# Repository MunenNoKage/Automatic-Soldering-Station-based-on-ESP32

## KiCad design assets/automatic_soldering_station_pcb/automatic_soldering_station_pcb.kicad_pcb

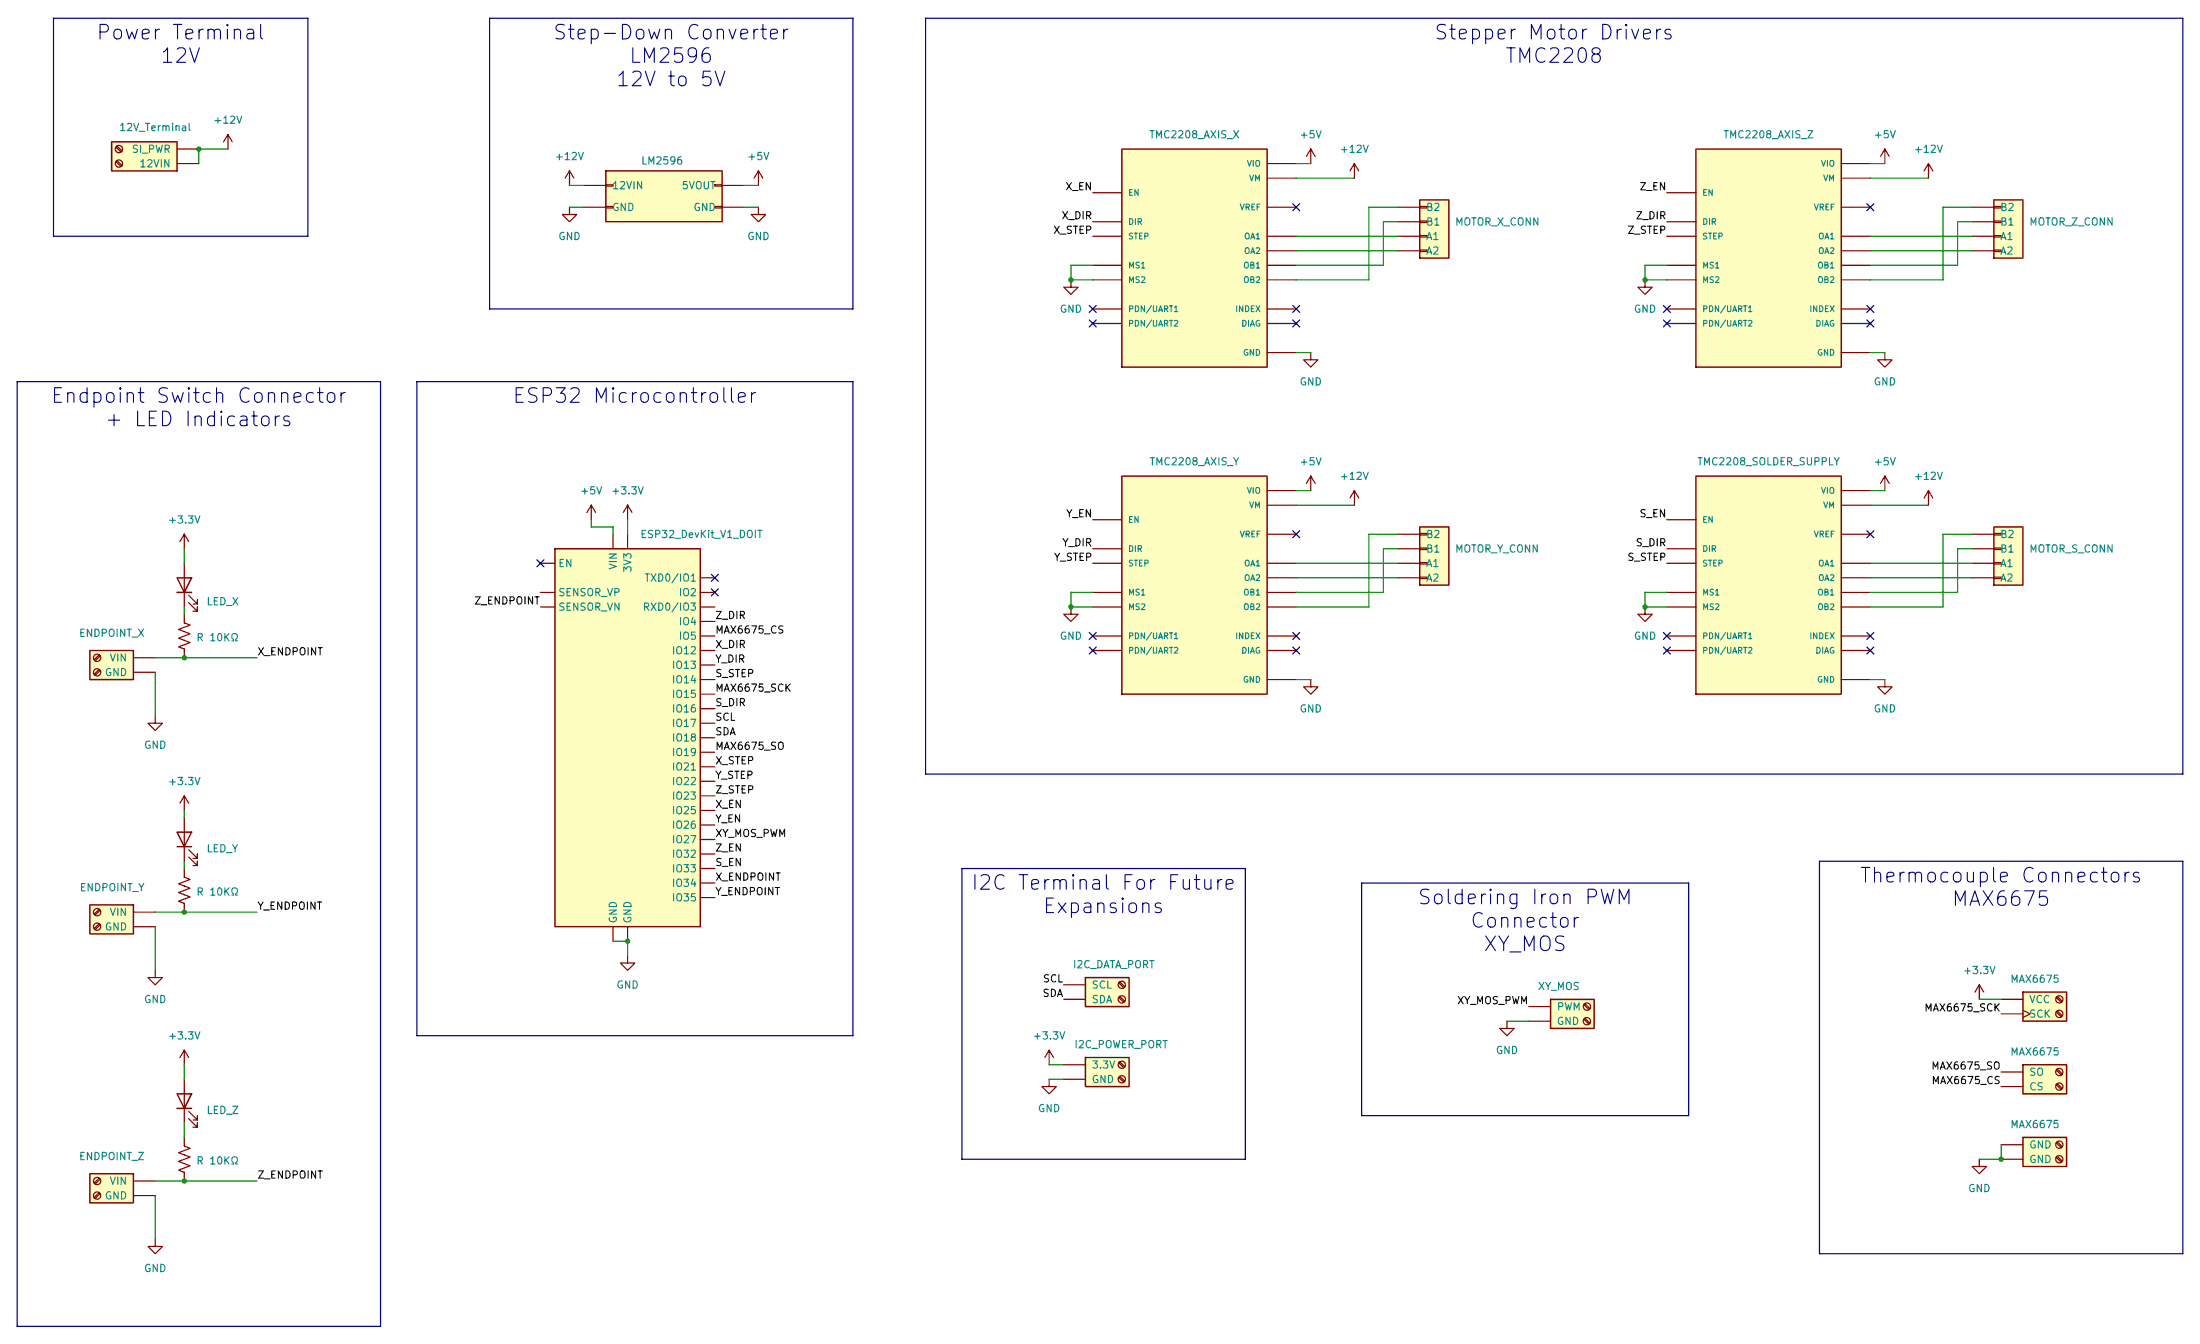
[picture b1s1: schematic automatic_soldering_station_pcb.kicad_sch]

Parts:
12V2: 12V_Terminal; TerminalBlock_MetzConnect_Type055_RT01502HDWU_1x02_P5.00mm_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
D1: LED_X; LED_D5.0mm
D2: LED_Y; LED_D5.0mm
D3: LED_Z; LED_D5.0mm
ENDPOINT_X1: ENDPOINT_X; TerminalBlock_MetzConnect_Type055_RT01502HDWU_1x02_P5.00mm_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
ENDPOINT_Y1: ENDPOINT_Y; TerminalBlock_MetzConnect_Type055_RT01502HDWU_1x02_P5.00mm_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
ENDPOINT_Y2: I2C_POWER_PORT; TerminalBlock_MetzConnect_Type055_RT01502HDWU_1x02_P5.00mm_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
ENDPOINT_Z1: ENDPOINT_Z; TerminalBlock_MetzConnect_Type055_RT01502HDWU_1x02_P5.00mm_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
ESP32_DevKit_V1_DOIT1: ESP32_DevKit_V1_DOIT; esp32_devkit_v1_doit
J1: XY_MOS; TerminalBlock_MetzConnect_Type055_RT01502HDWU_1x02_P5.00mm_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
J2, J3, J4: MAX6675; TerminalBlock_MetzConnect_Type055_RT01502HDWU_1x02_P5.00mm_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
J5: I2C_DATA_PORT; TerminalBlock_MetzConnect_Type055_RT01502HDWU_1x02_P5.00mm_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
LM2596: LM2596; LM2596_Board
MOTOR_S_CONN1: MOTOR_S_CONN; JST_PH_B4B-PH-K_1x04_P2.00mm_Vertical
MOTOR_X_CONN1: MOTOR_X_CONN; JST_PH_B4B-PH-K_1x04_P2.00mm_Vertical
MOTOR_Y_CONN1: MOTOR_Y_CONN; JST_PH_B4B-PH-K_1x04_P2.00mm_Vertical
MOTOR_Z_CONN1: MOTOR_Z_CONN; JST_PH_B4B-PH-K_1x04_P2.00mm_Vertical
R1, R2, R3: R 10KΩ; R_Axial_DIN0207_L6.3mm_D2.5mm_P7.62mm_Horizontal
TMC2208_AXIS_S1: TMC2208_SOLDER_SUPPLY; MODULE_TMC2208_SILENTSTEPSTICK
TMC2208_AXIS_X1: TMC2208_AXIS_X; MODULE_TMC2208_SILENTSTEPSTICK
TMC2208_AXIS_Y1: TMC2208_AXIS_Y; MODULE_TMC2208_SILENTSTEPSTICK
TMC2208_AXIS_Z1: TMC2208_AXIS_Z; MODULE_TMC2208_SILENTSTEPSTICK

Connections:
+3.3V: D1.2 (A), D2.2 (A), D3.2 (A), ENDPOINT_Y2.1 (3.3V), ESP32_DevKit_V1_DOIT1.16 (3V3), J3.1 (VCC)
+5V: ESP32_DevKit_V1_DOIT1.15 (VIN), LM2596.2 (5VOUT), TMC2208_AXIS_S1.JP2_7 (VIO), TMC2208_AXIS_X1.JP2_7 (VIO), TMC2208_AXIS_Y1.JP2_7 (VIO), TMC2208_AXIS_Z1.JP2_7 (VIO)
+12V: 12V2.1 (12VIN), 12V2.2 (SI_PWR), LM2596.0 (12VIN), TMC2208_AXIS_S1.JP2_1 (VM), TMC2208_AXIS_X1.JP2_1 (VM), TMC2208_AXIS_Y1.JP2_1 (VM), TMC2208_AXIS_Z1.JP2_1 (VM)
/MAX6675_CS: ESP32_DevKit_V1_DOIT1.23 (IO5), J4.2 (CS)
/MAX6675_SCK: ESP32_DevKit_V1_DOIT1.18 (IO15), J3.2 (SCK)
/MAX6675_SO: ESP32_DevKit_V1_DOIT1.25 (IO19), J4.1 (SO)
/SCL: ESP32_DevKit_V1_DOIT1.22 (IO17), J5.1 (SCL)
/SDA: ESP32_DevKit_V1_DOIT1.24 (IO18), J5.2 (SDA)
/S_DIR: ESP32_DevKit_V1_DOIT1.21 (IO16), TMC2208_AXIS_S1.JP1_1 (DIR)
/S_EN: ESP32_DevKit_V1_DOIT1.7 (IO33), TMC2208_AXIS_S1.JP1_8 (EN)
/S_STEP: ESP32_DevKit_V1_DOIT1.11 (IO14), TMC2208_AXIS_S1.JP1_2 (STEP)
/XY_MOS_PWM: ESP32_DevKit_V1_DOIT1.10 (IO27), J1.1 (PWM)
/X_DIR: ESP32_DevKit_V1_DOIT1.12 (IO12), TMC2208_AXIS_X1.JP1_1 (DIR)
/X_EN: ESP32_DevKit_V1_DOIT1.8 (IO25), TMC2208_AXIS_X1.JP1_8 (EN)
/X_ENDPOINT: ENDPOINT_X1.1 (VIN), ESP32_DevKit_V1_DOIT1.4 (IO34), R1.2
/X_STEP: ESP32_DevKit_V1_DOIT1.26 (IO21), TMC2208_AXIS_X1.JP1_2 (STEP)
/Y_DIR: ESP32_DevKit_V1_DOIT1.13 (IO13), TMC2208_AXIS_Y1.JP1_1 (DIR)
/Y_EN: ESP32_DevKit_V1_DOIT1.9 (IO26), TMC2208_AXIS_Y1.JP1_8 (EN)
/Y_ENDPOINT: ENDPOINT_Y1.1 (VIN), ESP32_DevKit_V1_DOIT1.5 (IO35), R2.2
/Y_STEP: ESP32_DevKit_V1_DOIT1.29 (IO22), TMC2208_AXIS_Y1.JP1_2 (STEP)
/Z_DIR: ESP32_DevKit_V1_DOIT1.20 (IO4), TMC2208_AXIS_Z1.JP1_1 (DIR)
/Z_EN: ESP32_DevKit_V1_DOIT1.6 (IO32), TMC2208_AXIS_Z1.JP1_8 (EN)
/Z_ENDPOINT: ENDPOINT_Z1.1 (VIN), ESP32_DevKit_V1_DOIT1.3 (SENSOR_VN), R3.2
/Z_STEP: ESP32_DevKit_V1_DOIT1.30 (IO23), TMC2208_AXIS_Z1.JP1_2 (STEP)
GND: ENDPOINT_X1.2 (GND), ENDPOINT_Y1.2 (GND), ENDPOINT_Y2.2 (GND), ENDPOINT_Z1.2 (GND), ESP32_DevKit_V1_DOIT1.14 (GND), ESP32_DevKit_V1_DOIT1.17 (GND), J1.2 (GND), J2.1 (GND), J2.2 (GND), LM2596.1 (GND), LM2596.3 (GND), TMC2208_AXIS_S1.JP1_6 (MS2), TMC2208_AXIS_S1.JP1_7 (MS1), TMC2208_AXIS_S1.JP2_2 (GND), TMC2208_AXIS_S1.JP2_8 (GND), TMC2208_AXIS_X1.JP1_6 (MS2), TMC2208_AXIS_X1.JP1_7 (MS1), TMC2208_AXIS_X1.JP2_2 (GND), TMC2208_AXIS_X1.JP2_8 (GND), TMC2208_AXIS_Y1.JP1_6 (MS2), TMC2208_AXIS_Y1.JP1_7 (MS1), TMC2208_AXIS_Y1.JP2_2 (GND), TMC2208_AXIS_Y1.JP2_8 (GND), TMC2208_AXIS_Z1.JP1_6 (MS2), TMC2208_AXIS_Z1.JP1_7 (MS1), TMC2208_AXIS_Z1.JP2_2 (GND), TMC2208_AXIS_Z1.JP2_8 (GND)
unnamed: D1.1 (K), R1.1
unnamed: D2.1 (K), R2.1
unnamed: D3.1 (K), R3.1
unnamed: MOTOR_S_CONN1.2 (A1), TMC2208_AXIS_S1.JP2_4 (OA1)
unnamed: MOTOR_S_CONN1.1 (A2), TMC2208_AXIS_S1.JP2_3 (OA2)
unnamed: MOTOR_S_CONN1.3 (B1), TMC2208_AXIS_S1.JP2_5 (OB1)
unnamed: MOTOR_S_CONN1.4 (B2), TMC2208_AXIS_S1.JP2_6 (OB2)
unnamed: MOTOR_X_CONN1.2 (A1), TMC2208_AXIS_X1.JP2_4 (OA1)
unnamed: MOTOR_X_CONN1.1 (A2), TMC2208_AXIS_X1.JP2_3 (OA2)
unnamed: MOTOR_X_CONN1.3 (B1), TMC2208_AXIS_X1.JP2_5 (OB1)
unnamed: MOTOR_X_CONN1.4 (B2), TMC2208_AXIS_X1.JP2_6 (OB2)
unnamed: MOTOR_Y_CONN1.2 (A1), TMC2208_AXIS_Y1.JP2_4 (OA1)
unnamed: MOTOR_Y_CONN1.1 (A2), TMC2208_AXIS_Y1.JP2_3 (OA2)
unnamed: MOTOR_Y_CONN1.3 (B1), TMC2208_AXIS_Y1.JP2_5 (OB1)
unnamed: MOTOR_Y_CONN1.4 (B2), TMC2208_AXIS_Y1.JP2_6 (OB2)
unnamed: MOTOR_Z_CONN1.2 (A1), TMC2208_AXIS_Z1.JP2_4 (OA1)
unnamed: MOTOR_Z_CONN1.1 (A2), TMC2208_AXIS_Z1.JP2_3 (OA2)
unnamed: MOTOR_Z_CONN1.3 (B1), TMC2208_AXIS_Z1.JP2_5 (OB1)
unnamed: MOTOR_Z_CONN1.4 (B2), TMC2208_AXIS_Z1.JP2_6 (OB2)

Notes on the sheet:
Step-Down Converter LM2596 12V to 5V
ESP32 Microcontroller
Endpoint Switch Connector + LED Indicators
I2C Terminal For Future Expansions
Thermocouple Connectors MAX6675
Soldering Iron PWM Connector XY_MOS
Power Terminal 12V
Stepper Motor Drivers TMC2208

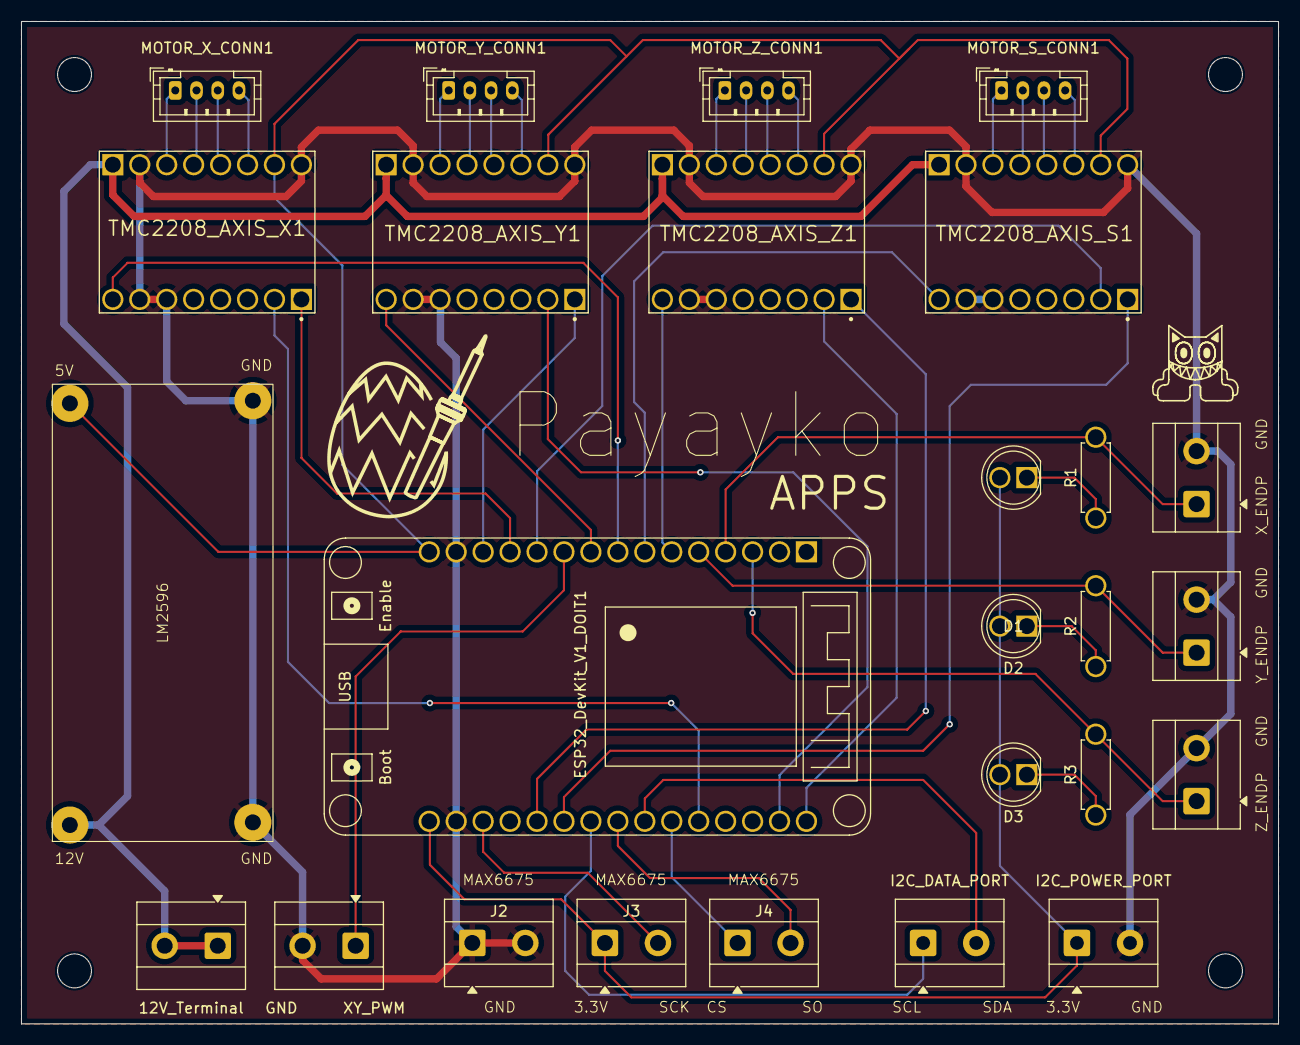
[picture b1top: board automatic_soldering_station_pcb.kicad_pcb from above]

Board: 2 copper layers, 118.5 x 94.5 mm, 30 parts (0 on the bottom side), 44 nets.

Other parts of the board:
H1, H2, H3, H4: MountingHole_3.2mm_M3

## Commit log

2025-11-20 chore: update 3d models for pcb holder
2025-11-20 chore: remove all deprecated directories
2025-11-20 chore: remove deprecated gcode_executor
2025-11-23 feat: update acceleration and deceleration logic and control
2025-11-23 feat: make calibration and movements faster, fix calibration glitch on endpoint
2025-11-23 pcb: add pcb project with complete project scheme
2025-11-30 pcb: add autorouted results
2025-12-01 pcb: add buck converter and reroute pcb manually
2025-12-08 pcb: polish routing
2025-12-08 pcb: fix printer specific mistakes
2025-12-09 Add manual control
2025-12-09 feat: update web interface
2025-12-09 pcb: reduce size of pcb
2025-12-09 feat: control z-position manually
2025-12-09 chore: add max measured motor positions to Kconfig
2025-12-09 feat: board visualization and real-time position tracking
2025-12-12 feat: add limit checking
2025-12-12 feat: add manual solder feed control
2025-12-12 feat: Add setting origin
2025-12-12 fix: server problems
2025-12-12 fix: 💊 🐷 🕑
2025-12-13 edited coments
2025-12-13 feat: too many features
2025-12-20 feat: update visualization, make clickable
2026-01-01 feat: Add fsm_callbacks module
2026-01-01 feat: Add Configuration system & Initialization components modules
2026-01-09 pcb: add I2C terminal to schematic
2026-01-09 chore: add kicad temporally files to .gitignore
2026-01-09 pcb: update components placement and reduce pcb size
2026-01-09 pcb: change pcb for China manufacturing
2026-01-11 pcb: change power traces width from 0.2 to 0.7mm, update gerber files
2026-01-11 pcb: add ground plane
2026-01-11 pcb: small fixes of ground plane
2026-01-22 web: change info texts
2026-01-24 feat: Tracking temperature during execution & Add navigation buttons
2026-01-24 feat: Implement temperature tracking & Heating control
2026-01-24 fix: Implement transitions from heating
2026-01-24 feat: Implement MANUAL_HEATING state
2026-01-27 web: add Take Solder button
2026-01-29 fix: change the order of calibration
2026-02-01 dns: implement a captive portal
2026-02-01 changed pins for temperature sensor
2026-02-01 fix: version of dependency
2026-04-03 pcb: add pcb output files
2026-04-03 feat: add debounce for endpoints
2026-04-03 feat: add test sequences
    NOTE: THERE IS BUG that watchdog is triggered in test sequences, but they managed to complete despite that
